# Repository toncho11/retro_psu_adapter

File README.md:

# What is it?
A retro ATX power adapter for retro computers that focuses on the POWER GOOD (PG) signal (also called DCOK), voltage protection and diagnostic for old computers such as DEC VAX 3100 M38 and SGI Indy. This project can be used if your original power supply unit (PSU) has failed or you prefer not to use it.

An early Model AA prototype.

# Models
| Model | Status | Description |
|---|---|---|
| [Model_AA](https://github.com/toncho11/retro_psu_adapter/tree/main/Model_AA) | Available | Handles PG and delays. Provides light voltage protection and diagnostic. Does not handle the high current rails of the ATX PSU (except for 5V TAP), this is done by the DS1188. Its primary goal is allow the VAX 3100 M38 to boot reliably. The -9 volts are not supprted, but also no needed for booting. It seems the -9 volts are only for networking.|
| Model_BB | Planned | Same as Model_AA, but now it handles the high current rails from the ATX PSU. Adds fan connectors. Should disable PSU if a fan has stopped for more than 1 minute. Could support both VAX and Indy using the correct firmware (TBD). Add support for optional -9V?|
| Model_CC | Planned | Based on Model BB and it will support more features specific to SGI Indy |

# Disclaimer

**⚠️ WARNING: ELECTRICAL SHOCK, FIRE, AND EQUIPMENT DAMAGE HAZARD**

This project is provided **"AS IS", without any warranty or guarantee of safety, reliability, or fitness for a particular purpose.** To the extent permitted by applicable law, the author and individual contributors disclaim liability for personal injury, death, property damage, or equipment damage resulting from the assembly, modification, installation, or use of these PSU adapters.

**You build and use these adapters entirely at your own risk!** These adapters are experimental hardware intended for users with appropriate electronics knowledge and experience. They are **NOT certified safety devices** and must **NOT** be assumed to provide protection against electrical shock, fire, or equipment damage.

Electricity is dangerous and must never be taken lightly. Incorrect wiring, inadequate grounding, short circuits, or improper handling can cause serious injury, electric shock, fire, or permanent damage to your computer and its components.

Always observe the following safety precautions:

- **Never leave exposed or dangling wires.** Ensure all connections are properly insulated and secured.
- **Never touch a PCB or exposed electrical contacts while the system is powered on.**
- **Always disconnect the power supply from the mains before installing, modifying, or inspecting the adapter.** Allow time for internal capacitors to discharge.
- **Ensure the PSU is properly grounded** through its protective earth connection.
- **Ensure the computer's metal chassis is properly connected to protective earth.**
- **Verify all connections, pinouts, polarities, and voltage levels before powering on the computer.**
- **Never bypass protective grounding or other safety mechanisms.**

**A particularly dangerous situation can occur when an exposed conductive surface becomes energized due to a fault.** You may initially feel nothing if there is no effective current path through your body. However, touching another conductive or grounded surface with your hand, leg, or another part of your body can complete that path, allowing potentially lethal current to flow. **The absence of an electric shock does not mean a surface is safe to touch!**

**If you are unsure about any aspect of electrical safety, do not proceed without assistance from a qualified professional.**

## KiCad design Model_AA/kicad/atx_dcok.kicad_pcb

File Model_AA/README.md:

# Target

Model AA is primary designed for the DEC Vax station 3100 M38, but can be used for other computers that require a specific power good (DCOK) delay, protection and diagnostic. Diagnostic is via messages on the serial port from the Arduino.

The Protective Earth (PE) between the case and the PSU is not available on this photo. More images are available at: <a href="https://github.com/toncho11/retro_psu_adapter/tree/main/Model_AA/images">Images</a>

# Current functionality

The adapter monitor the power good (PG) of the ATX PSU. It also monitors the 5V rail neat the the motherboard connector. This is called 5V TAP. Once both of them have been stable for specific amount of time (1 second for example) the adapter sends a valid DC OK to the VAX. Pull down resistors are incorporated to avoid dangling signals and prevent accendental startup or shutdown. The card has two diagnostic leds - greend and red. TODO1

# How to build

* check the [VAX 3100 M38 PSU doc](https://github.com/toncho11/retro_psu_adapter/blob/main/docs/vax_3100_m38/vax_3100_M38_doc.md) to understand what voltages and max current you need
* find a compatible ATX power supply. A list is available [here](https://github.com/toncho11/retro_psu_adapter/blob/main/docs/vax_3100_m38/compatible_psu.md). Only the Antec model is tested. 
* Print pcb
* Check BOM, order components TODO2
* Order [DS1188 ATX splitter](https://www.amazon.com/clp/B01NBU2C64). Other splitters might be cheaper, but this one is the only one that seems to have really tick tracks that can sustain hight current. Ordering to Europe is expensive.
* Solder the electronic components
* Check [warnings section](https://github.com/toncho11/retro_psu_adapter/blob/main/Model_AA/README.md#warnings-and-important-notes-including-hardware-and-personal-safety-and-software) for personal and hardware safety and other important notes!!!
* Compile and install firmware on the Arduino Nano
* Connect the male 14 pin connector to both DS1188 and the ATX adapter. Use pins provided in the doc ... TODO for the DS118 and the PCB labels. 
* Tap into the 5V near the motherboard's connector and the GND - these are inputs for the PCB
* Calibrate the TAP 5V - ... TODO3
* Test before connecting to a motherboard

# Warnings and important notes (including hardware and personal **safety** and software)

* WARNING: External ATX PSU may leave chassis (you computer's case) unearthed! You are probably using an external ATX PSU that it is not touching the computer's case. An internal PSU is grounded and it touches the case. This grounds the case as well. An external PSU changes that. The case might still be grounded through the motherboard's several ground lines, but a proper Protective Earth (PE) line is still needed between the case and the ATX PSU!
* WARNING: A short circuit on the 5V TAP line and a ground can be very dangerous. The holes on the adapter for these lines are very close. You might either solder them together by error or simply touch them using loose wires. Your ATX protection will probably not trigger because it will be within the limits of the PSU power supply's overcurrent protection. The PSU will think you are simply consuming a lot of power. But cables will start melting, exposing these cables to touch other surfaces and creating even bigger problem after a few seconds.
* WARNING: External PSU may compromise internal computer cooling! In Vax 3100 M38 the fans of the PSU are responsible for cooling both the PSU and motherboard, HDDs, etc. Removing the old internal PSU removes this cooling mechanism. Not having an internal PSU means less heat is produced inside the case, but (some) cooling of the motherboard is still needed.
* WARNING: Arduino Nano can be powered on input pin +5VSB through the ATX PSU or through its USB port. Make sure you are not using both. This means that you might want to wait before soldering permanently the +5VSB line from the ATX to the Model AA adapter.
* WARNING: The Arduino firmware uses ATmega328P-specific low-level registers and interrupts (PINB, PORTB, PCINT0_vect) in order to provide a very fast cutt off in case of a problem. It may not work on other Arduino variants without modification. Verify compatibility and DCOK behavior before real use.
* VERIFY: The Arduino will read ATX's POWER GOOD (PG) as HIGH if PG > 3.0V. Verify that your PG > 3.0V.

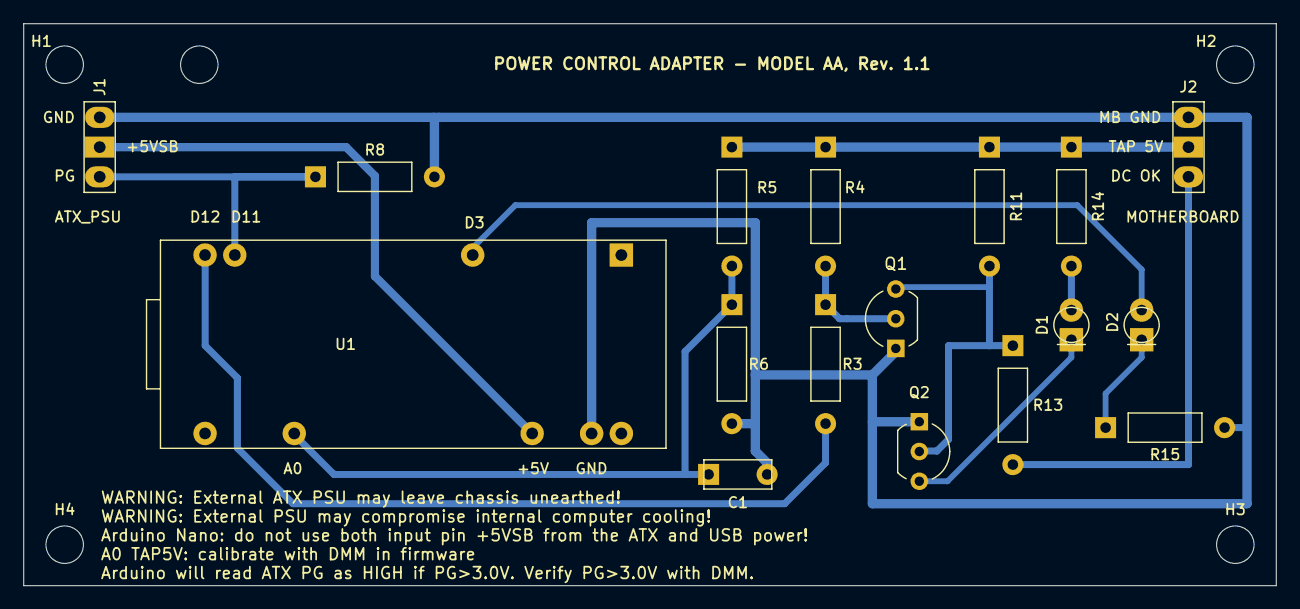
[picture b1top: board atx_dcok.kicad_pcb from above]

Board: 2 copper layers, 107.0 x 48.0 mm, 21 parts (0 on the bottom side), 13 nets.

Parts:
C1: 100nF ceramic; C_Disc_D5.0mm_W2.5mm_P5.00mm
D1: GREEN; LED_D3.0mm
D2: RED; LED_D3.0mm
H1, H2, H3, H4: MountingHole; MountingHole_3.2mm_M3
J1: ATX_PSU; PinHeader_1x03_P2.54mm_Vertical
J2: MOTHERBOARD; PinHeader_1x03_P2.54mm_Vertical
Q1: 2N3904; TO-92_Inline_Wide
Q2: 2N7000; TO-92_Inline_Wide
R3, R15: 1k; R_Axial_DIN0207_L6.3mm_D2.5mm_P10.16mm_Horizontal
R4: 22k; R_Axial_DIN0207_L6.3mm_D2.5mm_P10.16mm_Horizontal
R5: 47k 1%; R_Axial_DIN0207_L6.3mm_D2.5mm_P10.16mm_Horizontal
R6: 10k 1%; R_Axial_DIN0207_L6.3mm_D2.5mm_P10.16mm_Horizontal
R8: 100k; R_Axial_DIN0207_L6.3mm_D2.5mm_P10.16mm_Horizontal
R11: 10k; R_Axial_DIN0207_L6.3mm_D2.5mm_P10.16mm_Horizontal
R13: 100; R_Axial_DIN0207_L6.3mm_D2.5mm_P10.16mm_Horizontal
R14: 2.2k; R_Axial_DIN0207_L6.3mm_D2.5mm_P10.16mm_Horizontal
U1: Arduino_Nano_v3.x; Arduino_Nano

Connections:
/+5VSB: J1.1, U1.27
/A0: C1.1, R5.2, R6.1, U1.19
/COLLECTOR: Q1.3, Q2.2, R11.2, R13.1
/D3_RED: D2.2, U1.6
/D12_DRIVE: R3.2, U1.15
/DC_OK: J2.2, R13.2
/LED_A: D1.2, R14.2
/LED_K: D1.1, Q2.3
/PWR_OK: J1.2, R8.1, U1.14
/RED_K: D2.1, R15.1
/TAP_5V: J2.1, R4.1, R5.1, R11.1, R14.1
GND: C1.2, J1.3, J2.3, Q1.1, Q2.1, R6.2, R8.2, R15.2, U1.29
unnamed: Q1.2, R3.1, R4.2
